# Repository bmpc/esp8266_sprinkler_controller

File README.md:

# ESP8266 sprinkler controller
 
A WiFi lawn irrigation controller using an [ESP-12F WiFi module](https://docs.ai-thinker.com/_media/esp8266/docs/esp-12f_product_specification_en.pdf) to drive up to 4 sprinkler stations.
 
The sprinkler stations can be controlled and programmed remotely using [Home Assistant](https://www.home-assistant.io/).
 
The ESP8266 board communicates with Home Assistant using an [MQTT](https://mqtt.org/) broker on the local WiFi network. The ESP8266 listens to events in order to turn on/off and to program the schedule for each sprinkler station.
 
The controller is powered by a 9V battery as this is also the voltage required to activate the solenoids for each sprinkler. Being a battery powered device, the efficiency of the circuit is very important. The ESP8266 needs to be in deep sleep as much as possible and only wake up for activating/deactivating sprinkler stations.
 
There is also an interface mode that can be activated explicitly using Home Assistant. In interface mode, the ESP8266 will not go into deep sleep and is always ready to receive commands to activate/deactivate stations and configure the system. This mode is useful if we need to test a specific sprinkler station or if we need to trigger the stations manually.
 
The controller is also equipped with a reset button which will force the system to wake up from deep sleep, and go into interface mode (if enabled).
 
<div style="text-align:center">
 
</div>
 
## MQTT Topics
 
### Subscribe
 
| Topic                                | Payload format                                      | Payload example            | Retained |
| ------------------------------------ | --------------------------------------------------- | -------------------------- | -------- |
| `lawn-irrigation/station{x}/set`     | `{"on","off"}\|{"duration in milliseconds"}`        | `"on\|18000" ; "off"`      | false    |
| `lawn-irrigation/station{x}/config`  | `{"cron expression"}\|{"duration in milliseconds"}` | `"0 30 6 1-31/2 * *\|900"` | true     |
| `lawn-irrigation/interface-mode/set` | `{"on","off"}`                                      | `"on" ; "off"`             | true     |
| `lawn-irrigation/enabled/set`        | `{"on","off"}`                                      | `"on" ; "off"`             | true     |

### Publish
 
| Topic                                   | Payload format | Payload example | Retained |
| --------------------------------------- | -------------- | --------------- | -------- |
| `lawn-irrigation/station{x}/state`      | `{"on","off"}` | `"on" ; "off"`  | false    |
| `lawn-irrigation/interface-mode/state`  | `{"on","off"}` | `"on" ; "off"`  | false    |
| `lawn-irrigation/log`                   |  `<string>`    | `"log string"`  | true     |
 
## How to configure Home Assistant
 
The esp8266 sprinkler controller is configured from [Home Assistant](https://www.home-assistant.io/) using [MQTT switches](https://www.home-assistant.io/integrations/switch.mqtt/) and input fields.
 
As an example, here is my lawn irrigation card within the Home Assistant dashboard. I have three sprinkler stations configured:
 
<div style="text-align:center">
 
</div>
 
Each station is controlled by a different MQTT switch. The switches automatically display the station state and are also used to trigger the stations manually (provided that the controller is in **interface mode**).
 
Besides the station controller switches and CRON inputs, there are two additional switches to toggle:
- the interface mode
- the irrigation itself.
 When the irrigation controller is in **interface mode**, the ESP8266 will not go into deep sleep and the user can toggle the stations directly.
 
The irrigation toggle switch can be used to skip the programmed schedule. As an example, it is possible to disable the irrigation if rain is forecast for the next 12 hours or is has rained in the last 12h.
 
Apart from the switches, [Input Text Fields](https://www.home-assistant.io/integrations/input_text/) are used to configure the CRON expression and duration for each station. An automation is also required so that an MQTT event is published whenever the text field changes.
 
If a station is activated due to the configured cron expression schedule, the respective switch will be updated automatically with the current status as an MQTT event is sent from the controller whenever there is a station event.
 
You can find an example on how to configure these MQTT switches and text fields on the HA examples included in this repository:
- [configuration.yaml](/ha/configuration.yaml)
- [automations.yaml](/ha/automations.yaml)

## Circuit
 
### Power
 
Because the solenoids that activate the sprinklers require 9V to activate, this circuit is powered by a 9V battery (two 9V batteries in parallel to be precise). A voltage regulator is used to step down from 9v to 5v so that we can power some 5v ICs in the circuit. The ESP-12F requires 3.3V. Therefore, another voltage regulator was added to step down from 5v to 3.3v. This is not ideal, as there are two voltage regulators but in this case we require 3 different voltages and it would not be practical to have multiple batteries for the same circuit.
 
### Latching solenoids and the L293D ICs
 
There are two L293D ICs in this circuit. These are Quadruple Half-H Drivers that are designed to provide bidirectional drive currents. The L293D is also designed to drive inductive loads such as solenoids and motors. These ICs allow us to drive the 9v power lines to the solenoid with a 3.3v logic signal provided by the ESP8266.
 
A latching solenoid uses an electrical current pulse or internal permanent magnet material to maintain a set position without the constant application of power. Latching solenoids (also known as bistable solenoids) have two standard positions; de-energized with the plunger fully extended and de-energized with the plunger held in position by permanent magnets.
 
Electrical polarity is vital to proper latching a solenoid. As current flows in one direction, adds to the pull of the permanent magnet. Sending a current through the coil field in the opposite direction cancels the magnet’s attraction and releases the plunger from the latched position.
 
These L293D ICs are required in order to control our latching solenoids because we need to provide opposite polarities depending on if we are activating or deactivating the solenoid.
 
Each L293D can control two solenoids. Hence two L293D ICs were used to drive a total of 4 solenoids/sprinkler stations.
 
### The lack of pins and the 8-bit shift register
 
Because the ESP12-F only provides 11 GPIO digital pins, an 8-bit shift register was included so we can have more digital lines to drive the four possible solenoids/stations.
 
### Power Efficiency
 
This is a very important topic as this circuit is powered with standard 9v batteries. Depending on the battery type, usually a 9v battery has a capacity of around 300 mAh.
We must guarantee that our circuit is as efficient as possible. Ideally, the standby current of the circuit should not exceed 50uA. In these conditions, I estimate around 300 to 400 days on double 9v batteries.
 
Operating normally, without any changes to improve the efficiency of the circuit, the average current is about 90mA to 130mA. This includes the ESP8266 making WiFi requests, the two L293D ICs, the 8-bit shift register, and added the voltage regulators.
 
If we put the ESP8266 in deep sleep mode, the current drops to about 50mA to 60mA. This is still too high. The culprits are the two L293D ICs which have a very high quiescent current of about 30mA each.
 
Hence, to reduce the quiescent current of the L293D ICs, the power is supplied to these ICs only when stations need to be activated/deactivated. To achieve this, a simple NPN transistor is used to turn off the shift register and both L293D ICs. This transistor is driven by the ESP8266.
 
Even though the L293D ICs are not connected to power in standby mode, some pins can have enough voltage to pull the ESP-12F GPIO15 line HIGH thus preventing the ESP-12F from booting. The solution was to add a diode between the GPIO15 enable line and the L293D chip.
 
After these improvements, I measured the standby current of the circuit to around **20uA**.

### RTC accuracy on the ESP8266 

The max deep sleep time of the ESP-12F is about 3 to 4 hours. Therefore, the ESP needs to wake up every 3 hours or so and get right back to sleep if no action is required (no station needs to be started or stopped).

Also, it turns out that the ESP8266 doesn't have a very precise RTC (Real Time Clock). On a 3 hour period, my ESP8266 RTC would drift ahead around 14 minutes. Without a more precise clock, and considering our use case, we can just go back to sleep for the remaining time. 
 
### Schematic
 
<div style="text-align:center">
 
</div>
 
### BOM

| Part                                 | Qty |
| ------------------------------------ | --- |
| ESP-12F (ESP8266)                    | x1  |
| L293D (Quadruple Half-H Drivers)     | x2  |
| 74HC595 (8-bit shift register)       | x1  |
| MCP1702-5002E/TO (voltage regulator) | x1  |
| MCP1702-3302E/TO (voltage regulator) | x1  |
| SS8050CBU (NPN transistor)           | x1  |
| 100Ω resistor                        | x1  |
| 1k resistor                          | x4  |
| 10k resistor                         | x4  |
| 100 uF electrolytic capacitor        | x2  |
| 10 uF electrolytic capacitor         | x1  |
| 1 uF ceramic capacitor (104)         | x8  |
| SD101A (Schottky Diode)              | x1  |
| Switch (reset)                       | x1  |
| Barrel Jack Switch                   | x1  |
| Screw terminal                       | x4  |
| 9v battery                           | x2  |
| Rainbird solenoids                   | x3  |

## ESP8266 Project

The ESP8266 project was built using [Platform IO](https://docs.platformio.org/).

The platformio.ini file contains the default parameters to run the targets below. You can change this file or provide the parameters in the context of each `pio run <target>` command [(usage)](https://docs.platformio.org/en/latest/core/userguide/cmd_run.html#usage).

### Build

In order to compile and build the project you just need to run the following command.

`pio run build`

### Upload

You can upload the sketch using serial port or OTA (Over The Air).

The sketch is ready to receive (OTA) updates. In order to upload OTA, you need to set the `upload_port` parameter with the IP address or your ESP8266.
For serial upload, just se the `upload_port` parameter with the appropriate serial interface.

`pio run upload`

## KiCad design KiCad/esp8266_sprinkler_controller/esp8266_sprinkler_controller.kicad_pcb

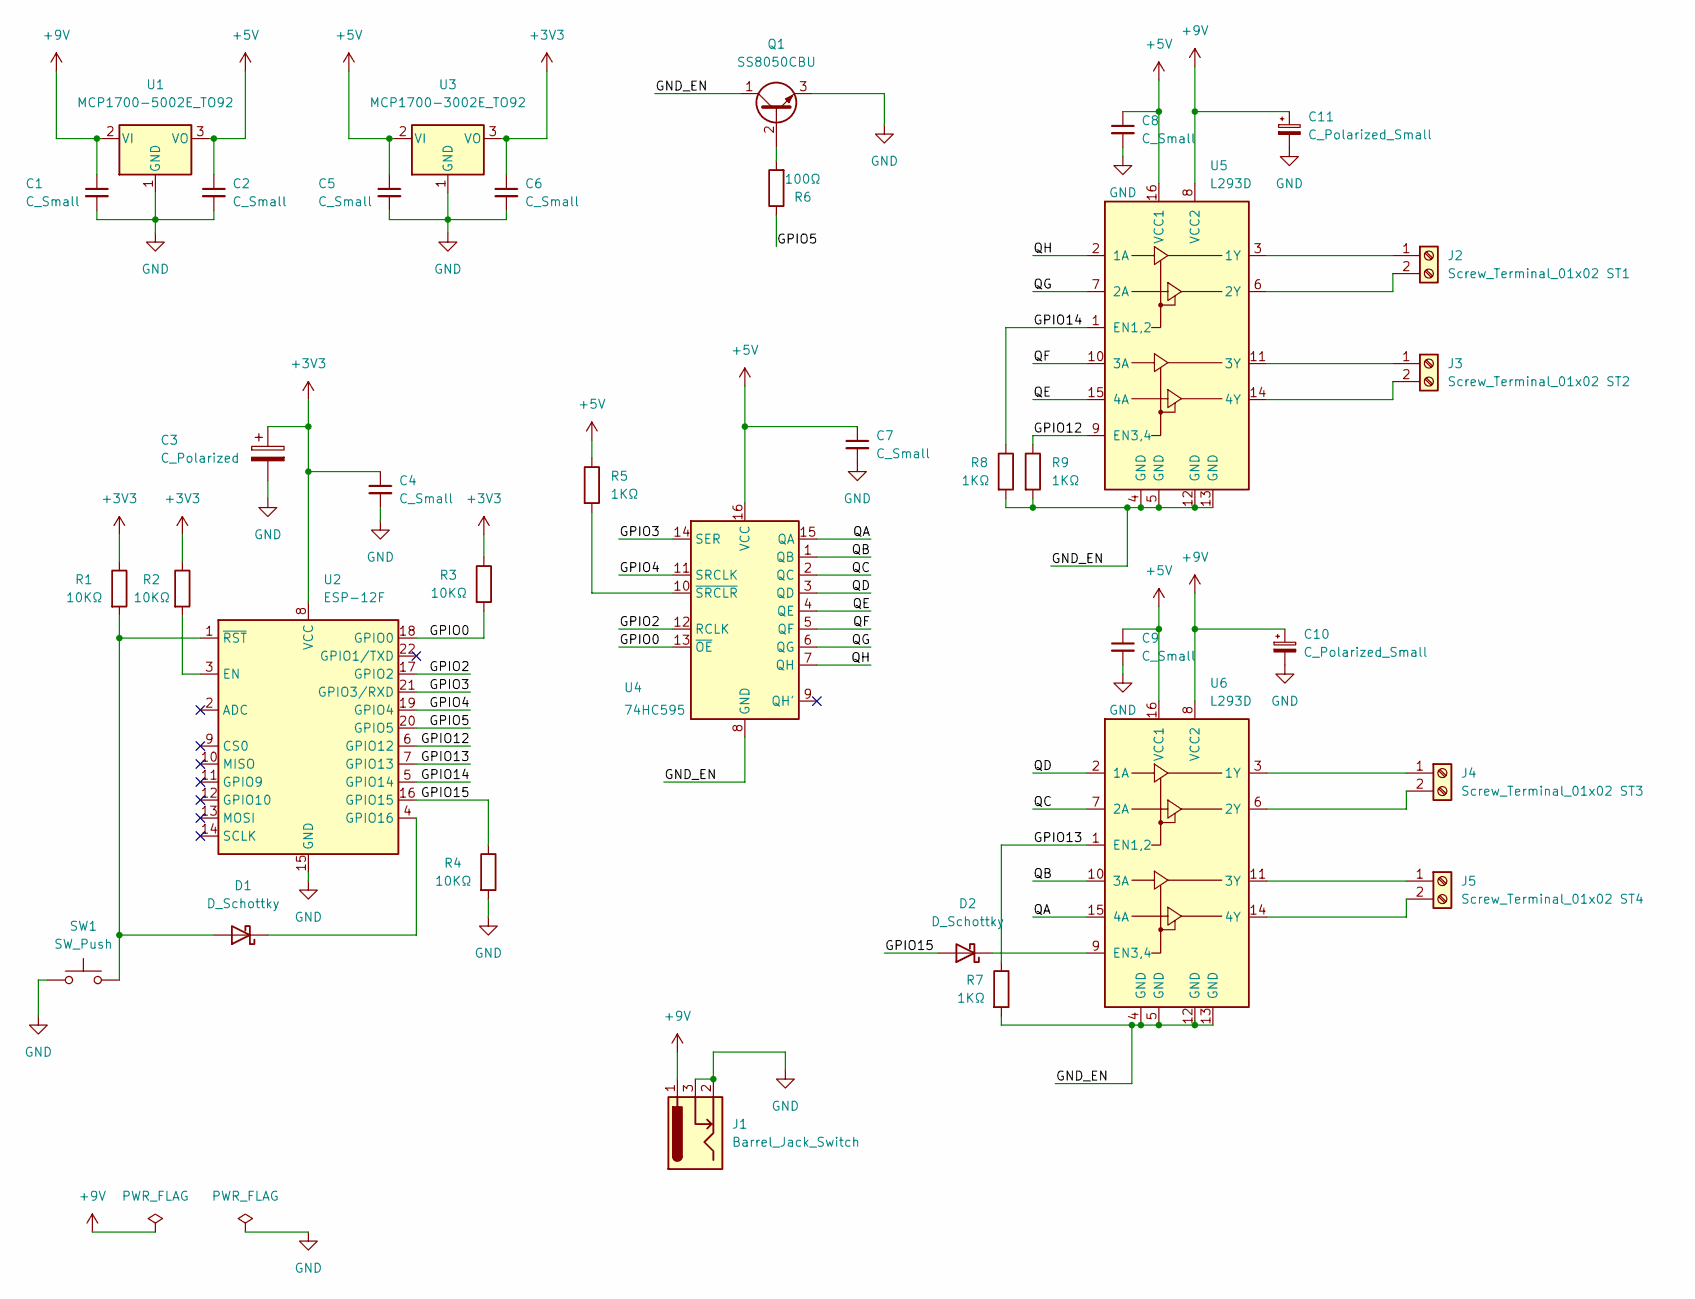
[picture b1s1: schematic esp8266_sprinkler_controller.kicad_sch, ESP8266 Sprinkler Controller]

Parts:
C1, C2, C4, C5, C6, C7, C8, C9: C_Small; C_Disc_D3.0mm_W1.6mm_P2.50mm
C3: C_Polarized; CP_Radial_D4.0mm_P2.00mm
C10, C11: C_Polarized_Small; CP_Radial_D4.0mm_P2.00mm
D1, D2: D_Schottky; D_A-405_P7.62mm_Horizontal
J1: Barrel_Jack_Switch; BarrelJack_Horizontal
J2: Screw_Terminal_01x02 ST1; TerminalBlock_bornier-2_P5.08mm
J3: Screw_Terminal_01x02 ST2; TerminalBlock_bornier-2_P5.08mm
J4: Screw_Terminal_01x02 ST3; TerminalBlock_bornier-2_P5.08mm
J5: Screw_Terminal_01x02 ST4; TerminalBlock_bornier-2_P5.08mm
Q1: SS8050CBU; TO-92
R1, R2, R3, R4: 10KΩ; R_Axial_DIN0207_L6.3mm_D2.5mm_P7.62mm_Horizontal
R5, R7, R8, R9: 1KΩ; R_Axial_DIN0207_L6.3mm_D2.5mm_P7.62mm_Horizontal
R6: 100Ω; R_Axial_DIN0207_L6.3mm_D2.5mm_P7.62mm_Horizontal
SW1: SW_Push; PinSocket_1x02_P2.54mm_Vertical
U1: MCP1700-5002E_TO92; TO-92
U2: ESP-12F; ESP-12E
U3: MCP1700-3002E_TO92; TO-92
U4: 74HC595; DIP-16_W7.62mm_Socket
U5, U6: L293D; DIP-16_W7.62mm_Socket

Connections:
+3V3: C3.1, C4.1, C6.1, R1.1, R2.1, R3.1, U2.8 (VCC), U3.3 (VO)
+5V: C2.1, C5.1, C7.1, C8.1, C9.1, R5.1, U1.3 (VO), U3.2 (VI), U4.16 (VCC), U5.16 (VCC1), U6.16 (VCC1)
+9V: C1.1, C10.1, C11.1, J1.1, U1.2 (VI), U5.8 (VCC2), U6.8 (VCC2)
/GND_EN: Q1.1 (C), R7.2, R8.2, R9.2, U4.8 (GND), U5.4 (GND), U5.5 (GND), U5.12 (GND), U5.13 (GND), U6.4 (GND), U6.5 (GND), U6.12 (GND), U6.13 (GND)
/GPIO0: R3.2, U2.18 (GPIO0), U4.13 (~OE)
/GPIO2: U2.17 (GPIO2), U4.12 (RCLK)
/GPIO3: U2.21 (GPIO3/RXD), U4.14 (SER)
/GPIO4: U2.19 (GPIO4), U4.11 (SRCLK)
/GPIO5: R6.1, U2.20 (GPIO5)
/GPIO12: R9.1, U2.6 (GPIO12), U5.9 (EN3,4)
/GPIO13: R7.1, U2.7 (GPIO13), U6.1 (EN1,2)
/GPIO14: R8.1, U2.5 (GPIO14), U5.1 (EN1,2)
/GPIO15: D2.2 (A), R4.1, U2.16 (GPIO15)
/QA: U4.15 (QA), U6.15 (4A)
/QB: U4.1 (QB), U6.10 (3A)
/QC: U4.2 (QC), U6.7 (2A)
/QD: U4.3 (QD), U6.2 (1A)
/QE: U4.4 (QE), U5.15 (4A)
/QF: U4.5 (QF), U5.10 (3A)
/QG: U4.6 (QG), U5.7 (2A)
/QH: U4.7 (QH), U5.2 (1A)
GND: C1.2, C2.2, C3.2, C4.2, C5.2, C6.2, C7.2, C8.2, C9.2, C10.2, C11.2, J1.2, J1.3, Q1.3 (E), R4.2, SW1.1, U1.1 (GND), U2.15 (GND), U3.1 (GND)
unnamed: D1.1 (K), U2.4 (GPIO16)
unnamed: D1.2 (A), R1.2, SW1.2, U2.1 (~RST)
unnamed: D2.1 (K), U6.9 (EN3,4)
unnamed: J2.1, U5.3 (1Y)
unnamed: J2.2, U5.6 (2Y)
unnamed: J3.1, U5.11 (3Y)
unnamed: J3.2, U5.14 (4Y)
unnamed: J4.1, U6.3 (1Y)
unnamed: J4.2, U6.6 (2Y)
unnamed: J5.1, U6.11 (3Y)
unnamed: J5.2, U6.14 (4Y)
unnamed: Q1.2 (B), R6.2
unnamed: R2.2, U2.3 (EN)
unnamed: R5.2, U4.10 (~SRCLR)

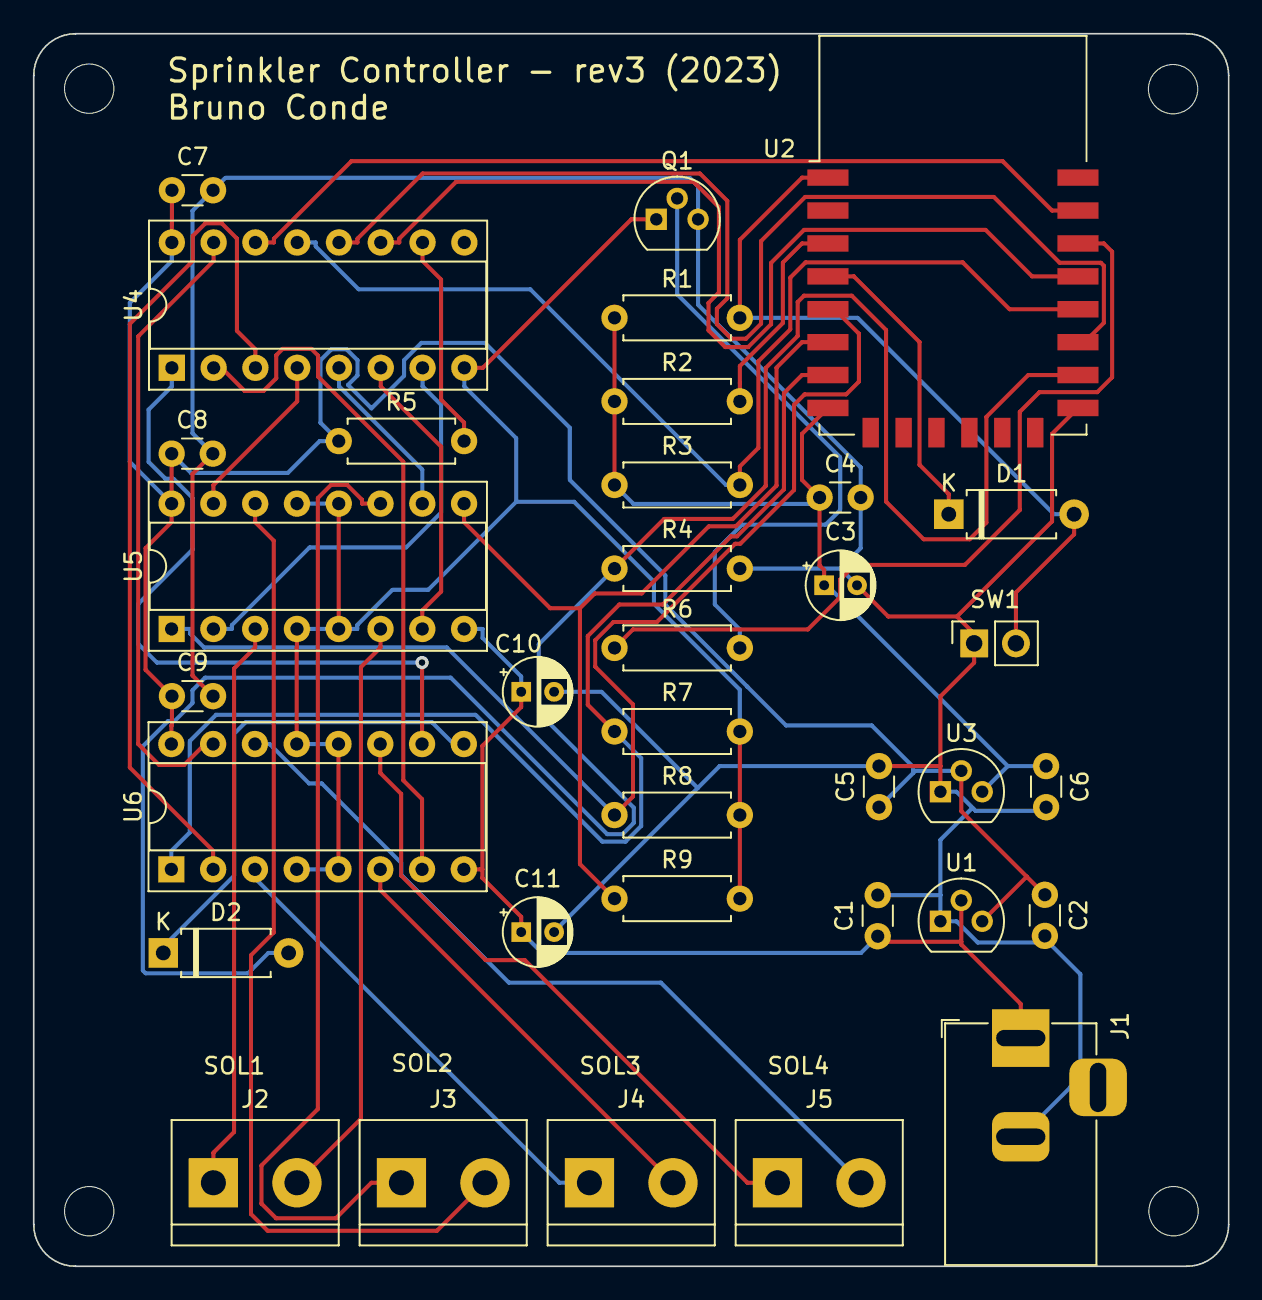
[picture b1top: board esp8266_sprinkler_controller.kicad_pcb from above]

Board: 2 copper layers, 72.6 x 74.9 mm, 39 parts (0 on the bottom side), 36 nets.

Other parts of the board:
Hole1, Hole2, Hole3, Hole4: MountingHole_3mm

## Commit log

2022-10-01 New version that properly handles latching solenoids using the L293 half-H drivers IC; Kicad schematic for circuit; New interaction with Home Assistant; ESP8266 Deep Sleep
2022-10-01 Updated .gitignore
2022-10-24 Researching a way to use less power when the circuit is in deep sleep; Updated Kicad schematic and pcb design
2022-11-22 Refactor esp8266 code; New Kicad schematic version (v2.0) to make the circuit battery efficient
2022-11-22 Removed old circuit image
2023-01-08 KiCad: Revision 3 of schematic abdnd PCB. Solved a couple of circuit problems: - Added a Schottky Diode between the reset line and GPIO16 so this pin is not shorted when the reset button is pressed. 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
    ESP8266: Force a loop call to the MQTT broker when interface_mode is not active
    as MQTT messages were not being published correctly because the ESP8266 would
    go into deep sleep before it finished processing the messages.
2023-01-21 There is a max deep sleep of around 3 hours on the ESP8266. Therefore, we need to wake every 3 hours, check for station events, and go right back to sleep if no station needs to be started/stoped.
2023-01-21 Added a README entry for the MAX deep sleep of the ESP8266
2023-01-22 Adding a new HA automation to disable irrigation when there is a rainy day
2023-01-22 Fix a typo on README
2024-06-02 Fixed small bugs; Added logs; Removed interface mode when there is no next event
2024-07-03 Fixed invalid logic when activating/deactivating stations
2024-08-10 Stations will now be enabled/disabled based on the schedule even if interface mode is ON. In other words, we can now use the spinkler controller always connected to power, without the need to sleep t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
2024-08-12 Improved logging
2024-08-13 Fixed bug where the station duration was being set to zero when it stops
2024-08-18 Fixed bug where the scheduled duration of a stations was being mixed with the active duration of a station
2024-09-21 Initializing MQTT when WiFI reconnects
2025-07-23 Solved a bug where mqtt topics were not being subscribed after an MQTT reconnect
2025-08-02 Adding README instructions to build and upload the project using platform IO
